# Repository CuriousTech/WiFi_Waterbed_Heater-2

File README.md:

# WiFi Waterbed Heater 2  
  
Discontinued, go here: [WiFiWaterbedHeater3](https://github.com/CuriousTech/WiFiWaterbedHeater3)

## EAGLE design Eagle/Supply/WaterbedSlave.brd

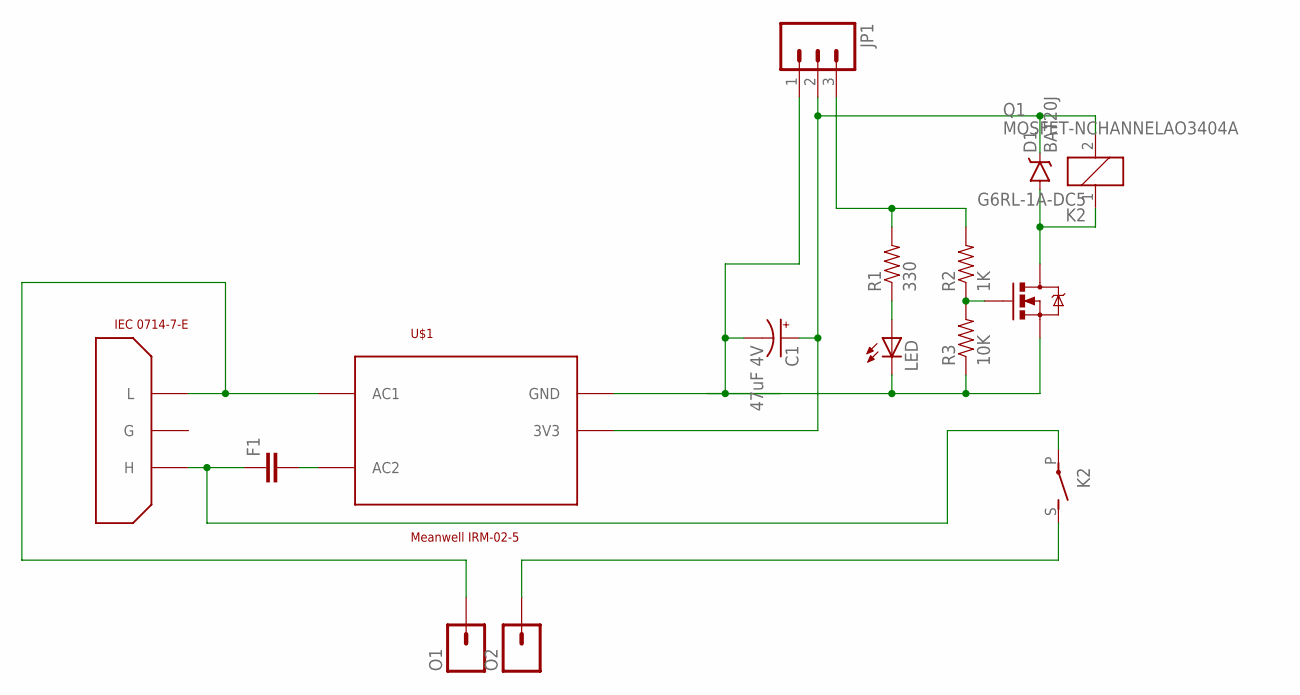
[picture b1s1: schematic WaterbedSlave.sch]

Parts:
C1: 47uF 4V; CPOL-RADIAL-10UF-25V
D1: BAT20J; SOD-323
F1: CAPPTH1; CAP-PTH-5MM
JP1: M03POLAR_LOCK; MOLEX-1X3_LOCK
K2: G6RL-1A-DC5; G6RS
LED: LEDCHIPLED_0805; CHIPLED_0805
O1, O2: M01PTH_2MM; 1X01_2MM
Q1: MOSFET-NCHANNELAO3404A; SOT23-3
R1: 330; 0805
R2: 1K; 0805
R3: 10K; 0805
U$1: Meanwell IRM-02-5; RAC02-3.3SC
U$3: IEC 0714-7-E; IEC

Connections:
3V3: C1.1 (+), D1.C, JP1.2, K2.2, U$1.GND (3V3)
GND: C1.2 (-), JP1.1, LED.C, Q1.2 (S), R3.1, U$1.3V3 (GND)
unnamed: O1.1, U$1.AC1, U$3.L
unnamed: F1.2, U$1.AC2
unnamed: K2.S, O2.1
unnamed: F1.1, K2.P, U$3.H
unnamed: D1.A, K2.1, Q1.3 (D)
unnamed: LED.A, R1.1
unnamed: JP1.3, R1.2, R2.2
unnamed: Q1.1 (G), R2.1, R3.2

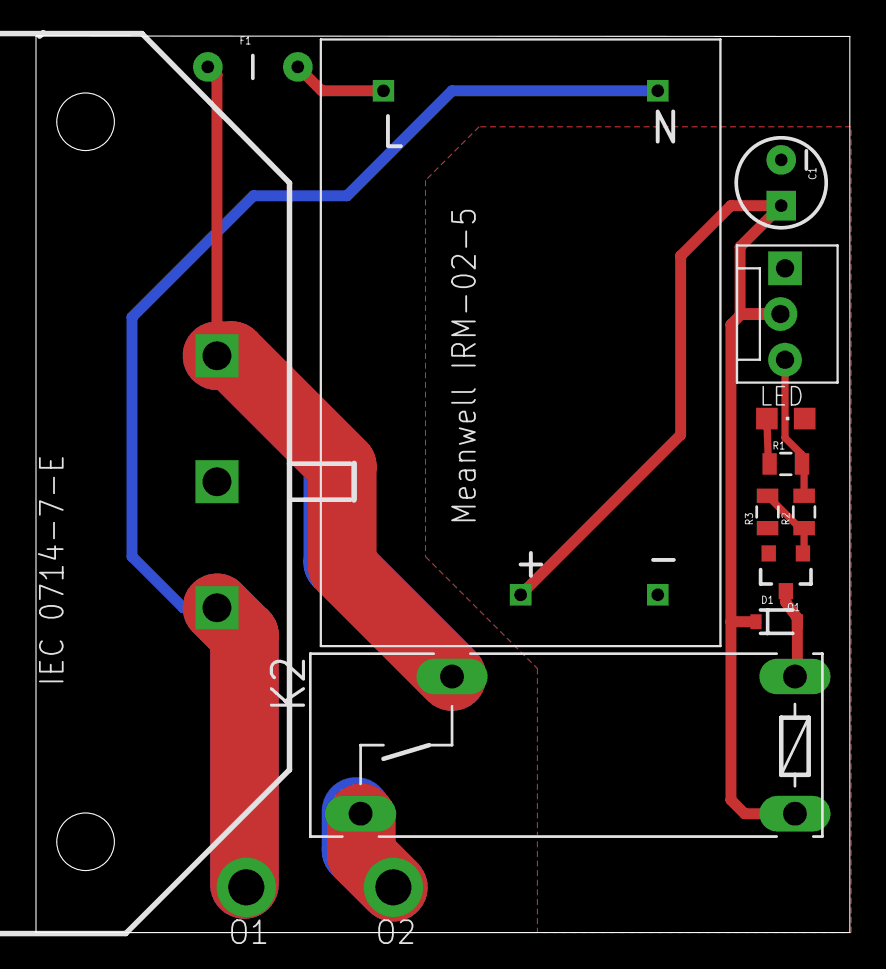
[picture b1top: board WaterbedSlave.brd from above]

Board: 2 copper layers, 45.2 x 49.8 mm, 14 parts (0 on the bottom side), 10 nets.

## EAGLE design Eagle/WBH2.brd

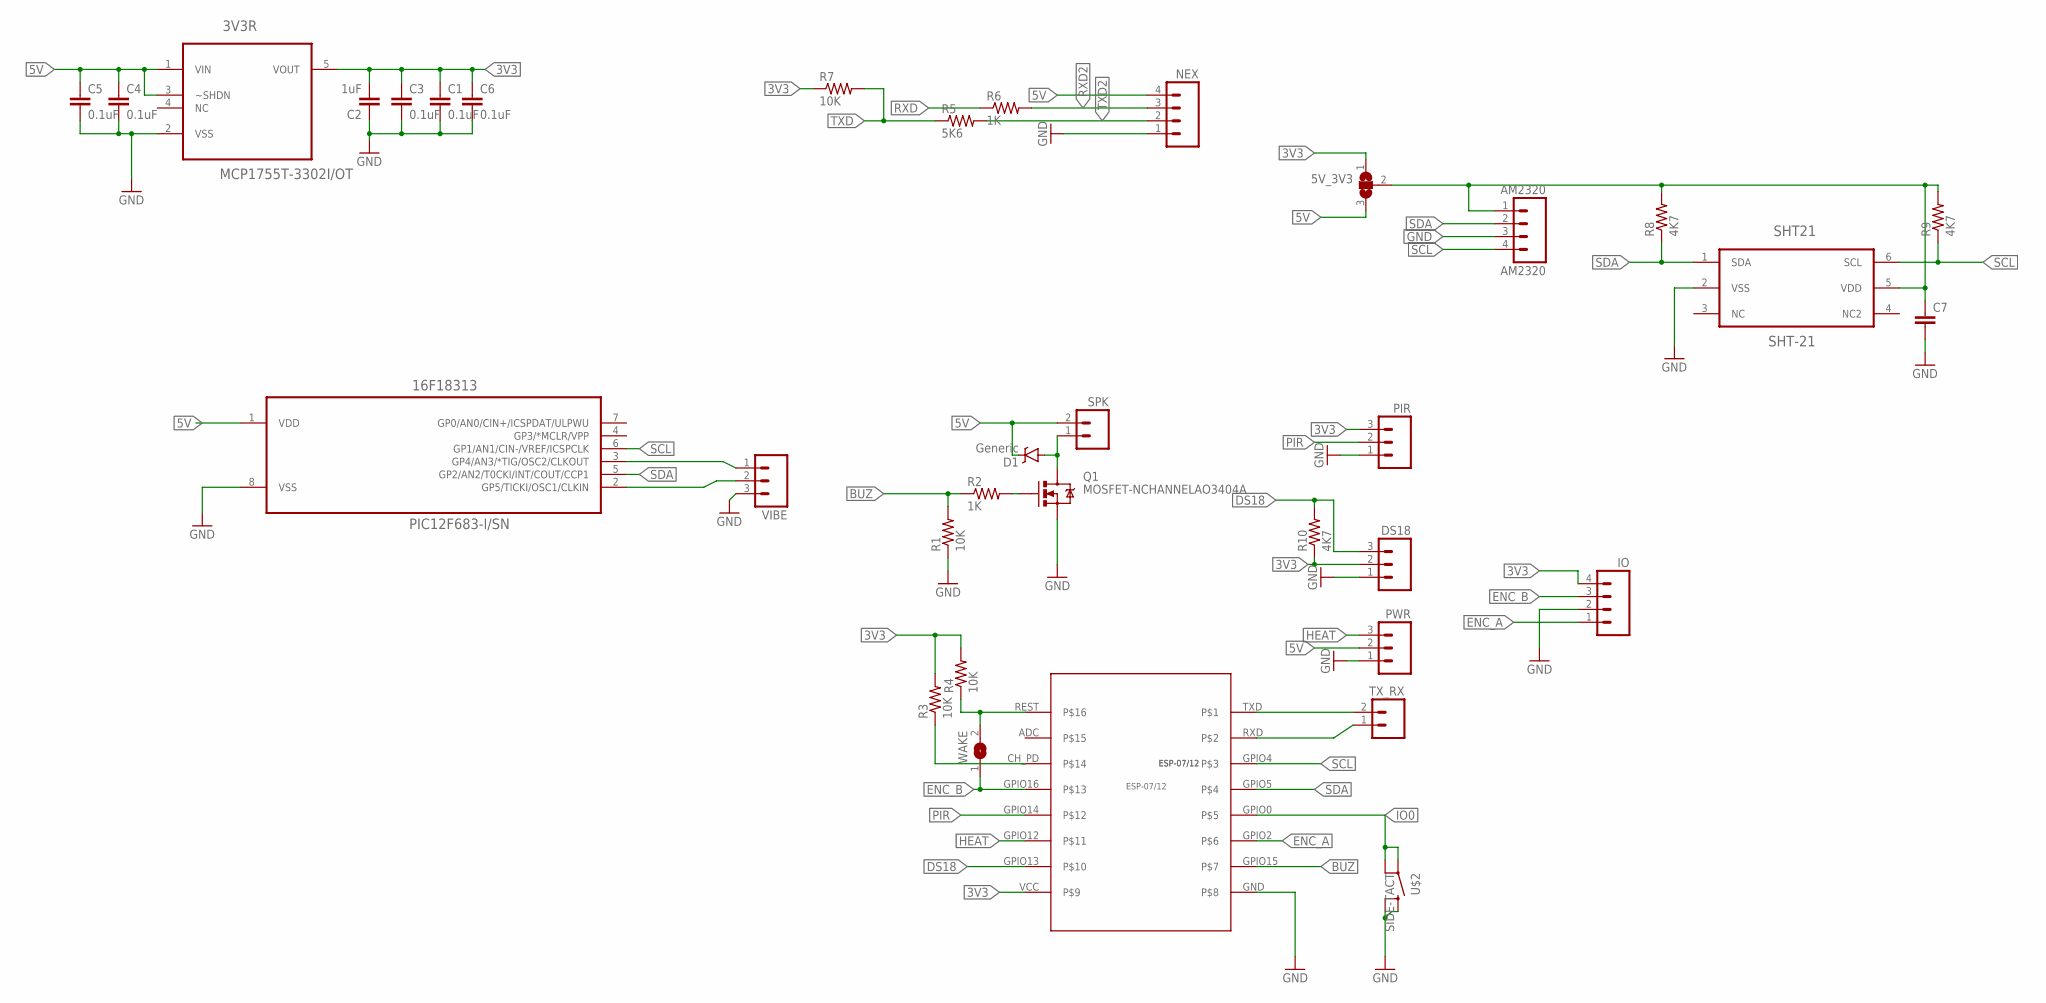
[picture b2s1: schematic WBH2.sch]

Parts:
3V3R: MCP1755T-3302I/OT; SOT95P270X145-5N
5V_3V3: SJ2W; SJ_2
16F18313: PIC12F683-I/SN; SOIC127P600X175-8N
AM2320: AM2320; 1X04
C1, C3, C4, C5, C6: 0.1uF; 0805
C2: 1uF; 0805
C7: CAP0603-CAP; 0603-CAP
D1: Generic; SOD-323
DS18: M03PTH; 1X03
IO: M04PTH; 1X04
NEX: M04PTH; 1X04
PIR: M03PTH; 1X03
PWR: M03PTH; 1X03
Q1: MOSFET-NCHANNELAO3404A; SOT23-3
R1, R3, R4, R7: 10K; 0805
R2, R6: 1K; 0805
R5: 5K6; 0805
R8, R9, R10: 4K7; 0805
SHT21: SHT-21; SHT21
SPK: M02PTH; 1X02
TX_RX: M02PTH; 1X02
U$1: ESP-07/12
U$2: SIDE-TACT
VIBE: M03PTH; 1X03
WAKE: SJ

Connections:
3V3: 3V3R.5 (VOUT), 5V_3V3.1, C1.1, C2.2, C3.1, C6.1, DS18.2, IO.4, PIR.3, R3.2, R4.2, R7.1, R10.1, U$1.VCC
5V: 3V3R.1 (VIN), 3V3R.3 (~SHDN), 5V_3V3.3, 16F18313.1 (VDD), C4.1, C5.1, D1.C, NEX.4, PWR.2, SPK.2
BUZ: R1.2, R2.1, U$1.GPIO15
DS18: DS18.3, R10.2, U$1.GPIO13
ENC_A: IO.1, U$1.GPIO2
ENC_B: IO.3, U$1.GPIO16, WAKE.1
GND: 3V3R.2 (VSS), 16F18313.8 (VSS), AM2320.3, C1.2, C2.1, C3.2, C4.2, C5.2, C6.2, C7.2, DS18.1, IO.2, NEX.1, PIR.1, PWR.1, Q1.2 (S), R1.1, SHT21.2 (VSS), U$1.GND, U$2.3 (2), U$2.4, VIBE.3
HEAT: PWR.3, U$1.GPIO12
IO0: U$1.GPIO0, U$2.1, U$2.2 (3)
unnamed: 16F18313.3 (GP4/AN3/*TIG/OSC2/CLKOUT), VIBE.1
unnamed: 16F18313.2 (GP5/TICKI/OSC1/CLKIN), VIBE.2
unnamed: D1.A, Q1.3 (D), SPK.1
unnamed: Q1.1 (G), R2.2
unnamed: R3.1, U$1.CH_PD
NC: SHT21.3 (NC)
PIR: PIR.2, U$1.GPIO14
PWR: 5V_3V3.2, AM2320.1, C7.1, R8.2, R9.2, SHT21.5 (VDD)
REST: R4.1, U$1.REST, WAKE.2
RXD: R6.1, TX_RX.1, U$1.RXD
RXD2: NEX.3, R6.2
SCL: 16F18313.6 (GP1/AN1/CIN-/VREF/ICSPCLK), AM2320.4, R9.1, SHT21.6 (SCL), U$1.GPIO4
SDA: 16F18313.5 (GP2/AN2/T0CKI/INT/COUT/CCP1), AM2320.2, R8.1, SHT21.1 (SDA), U$1.GPIO5
TXD: R5.1, R7.2, TX_RX.2, U$1.TXD
TXD2: NEX.2, R5.2

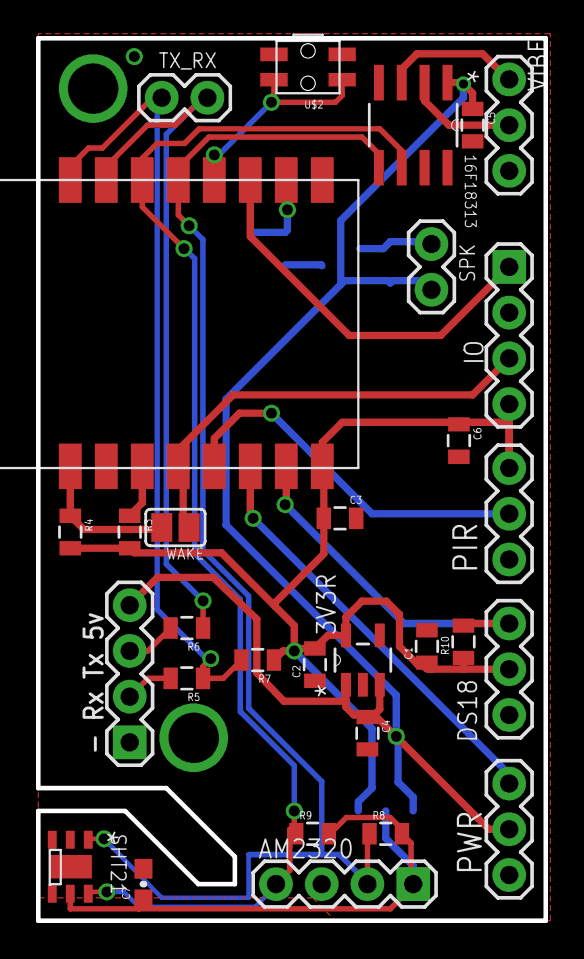
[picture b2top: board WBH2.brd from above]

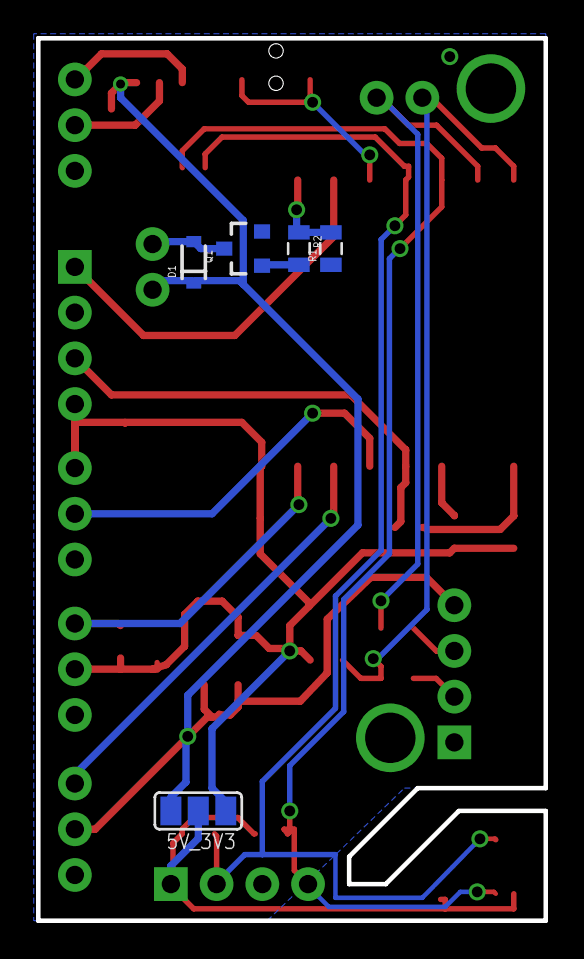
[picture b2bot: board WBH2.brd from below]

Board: 2 copper layers, 28.2 x 49.0 mm, 35 parts (5 on the bottom side), 23 nets.

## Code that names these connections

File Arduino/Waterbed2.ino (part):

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#define BTN      0 //  top
#define SDA      8
#define SCL      9
#define HEAT     11  // Heater output
#define DS18B20  12
#define MOTION   14  // PIR/mmWave sensor
#define RADAR_TX 16
#define RADAR_RX 17
#define TONE     40  // Speaker.  Beeps on powerup, but can also be controlled by another IoT or add an alarm clock.
#define ENC_A    26
#define ENC_B    33

#include <ld2410.h> // from Library Manager in Arduino IDE
#define RADAR_SERIAL Serial1
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#else

#define BTN      0 //  top
#define ENC_A    2
#define ESP_LED  2  //Blue LED on ESP12 (on low)
#define SDA      4
#define SCL      5
#define HEAT     12  // Heater output
#define DS18B20  13
#define MOTION   14  // PIR/mmWave sensor
#define TONE     15  // Speaker.  Beeps on powerup, but can also be controlled by another IoT or add an alarm clock.
#define ENC_B    16

#endif

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  pinMode(TONE, OUTPUT);
  digitalWrite(TONE, LOW);
  pinMode(BTN, INPUT_PULLUP);
  pinMode(HEAT, OUTPUT);
  digitalWrite(HEAT, LOW);
#ifdef ESP_LED
  pinMode(ESP_LED, OUTPUT);
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      state++;
      break;
    case 2:
      state = 0; // 1 second rest
      return;
  }

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
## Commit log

2020-01-30 Added schedule and alarm pages
2020-02-29 Looks like many changes
2020-02-29 Making sure it's all synced
2020-08-04 Changed to seconds accum instead of cost
2020-08-04 Changes for month chart mostly
2020-08-04 Month chart changes
2020-11-19 Notification popup
2020-11-19 Notifications
2020-12-12 Added ETA display
2020-12-12 Added overshoot save
2020-12-12 Changed tone to music class
2020-12-12 ETA experiments
2021-01-25 fix divide by 0
2023-01-26 Dual season schedules
2023-01-26 Dual season stuff
2023-01-26 Merged structs
2023-01-26 Changed schedule and SmartConnect
2023-01-26 Dual season and SmartConnect
2024-06-10 Added ESP32 support and LD2410 (req ESP32)
2024-06-10 Uses Preferences for ESP32
2024-06-10 Added ESP32 support, LD2410 (req ESP32), 4 season temp set

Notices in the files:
Arduino/Waterbed2.ino:
The MIT License (MIT)
Copyright (c) 2020 by Greg Cunningham, CuriousTech
parts and their libraries:
SparkFun-Connectors: Licensing: Creative Commons ShareAlike 4.0 International - https://creativecommons.org/licenses/by-sa/4.0
SparkFun-Connectors: Licensing: CC v3.0 Share-Alike You are welcome to use this library for commercial purposes.
